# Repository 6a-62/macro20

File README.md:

# macro20

- 20 keys, intended for numpad/macropad layouts
- Designed for Pro Micro controller boards
- I2C header intended for 0.91 128\*32 OLED display
- PWM header for RGB LED lighting strip

Compatible with [QMK](https://qmk.fm)

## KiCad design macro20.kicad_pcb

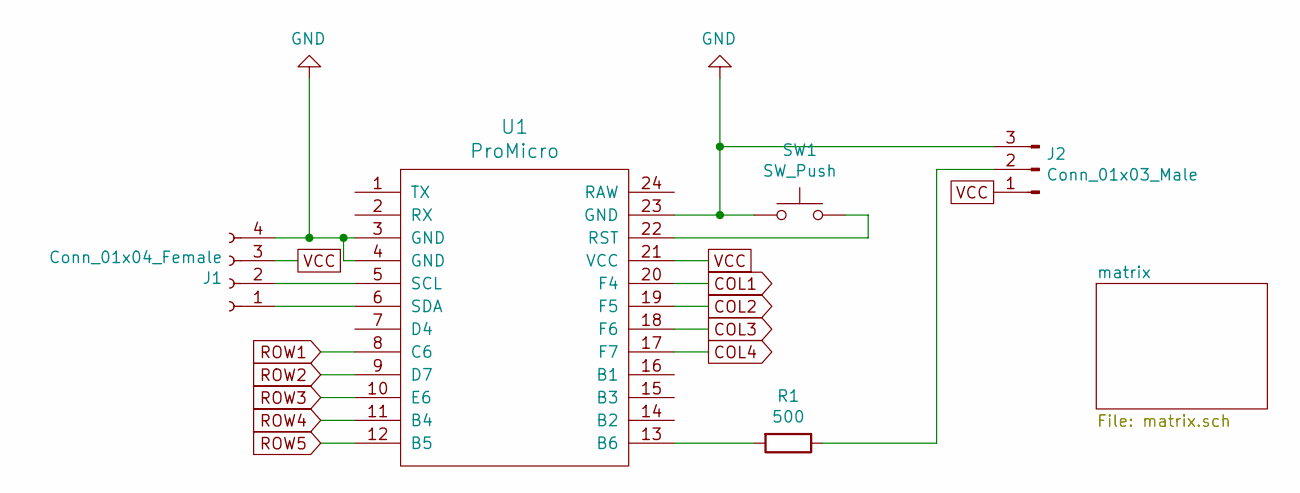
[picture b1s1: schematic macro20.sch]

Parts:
J1: Conn_01x04_Female; PinSocket_1x04_P2.54mm_Vertical
J2: Conn_01x03_Male; PinHeader_1x03_P2.54mm_Vertical
R1: 500; R_Axial_DIN0204_L3.6mm_D1.6mm_P5.08mm_Horizontal
SW1: SW_Push; SW_PUSH_6mm
U1: ProMicro

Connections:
COL1: U1.20 (F4); also elsewhere on the board
COL2: U1.19 (F5); also elsewhere on the board
COL3: U1.18 (F6); also elsewhere on the board
COL4: U1.17 (F7); also elsewhere on the board
GND: J1.4, J2.3, SW1.1, U1.3 (GND), U1.4 (GND), U1.23 (GND)
unnamed: J1.1, U1.6 (SDA)
unnamed: J1.2, U1.5 (SCL)
unnamed: J2.2, R1.1
unnamed: R1.2, U1.13 (B6)
unnamed: SW1.2, U1.22 (RST)
ROW1: U1.8 (C6); also elsewhere on the board
ROW2: U1.9 (D7); also elsewhere on the board
ROW3: U1.10 (E6); also elsewhere on the board
ROW4: U1.11 (B4); also elsewhere on the board
ROW5: U1.12 (B5); also elsewhere on the board
VCC: J1.3, J2.1, U1.21 (VCC)

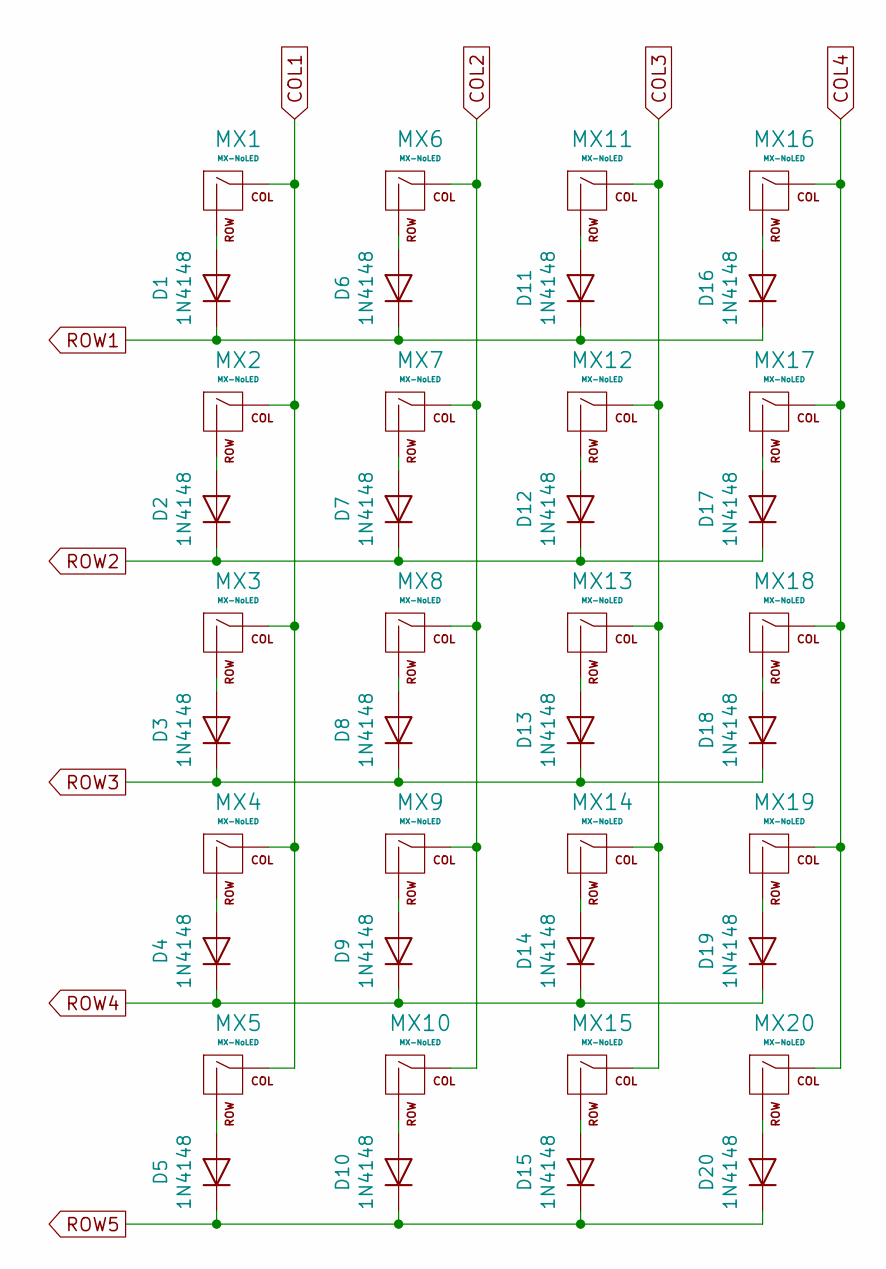
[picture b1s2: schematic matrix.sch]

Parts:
D1, D2, D3, D4, D5, D6, D7, D8, D9, D10, D11, D12, D13, D14, D15, D16, D17, D18, D19, D20: 1N4148; D_DO-35_SOD27_P7.62mm_Horizontal
MX1, MX2, MX3, MX4, MX5, MX6, MX7, MX8, MX9, MX10, MX11, MX12, MX13, MX14, MX15, MX16, MX17, MX18, MX19, MX20: MX-NoLED; MXOnly-1U-NoLED

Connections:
COL1: MX1.1 (COL), MX2.1 (COL), MX3.1 (COL), MX4.1 (COL), MX5.1 (COL); also elsewhere on the board
COL2: MX6.1 (COL), MX7.1 (COL), MX8.1 (COL), MX9.1 (COL), MX10.1 (COL); also elsewhere on the board
COL3: MX11.1 (COL), MX12.1 (COL), MX13.1 (COL), MX14.1 (COL), MX15.1 (COL); also elsewhere on the board
COL4: MX16.1 (COL), MX17.1 (COL), MX18.1 (COL), MX19.1 (COL), MX20.1 (COL); also elsewhere on the board
unnamed: D1.2 (A), MX1.2 (ROW)
unnamed: D2.2 (A), MX2.2 (ROW)
unnamed: D3.2 (A), MX3.2 (ROW)
unnamed: D4.2 (A), MX4.2 (ROW)
unnamed: D5.2 (A), MX5.2 (ROW)
unnamed: D6.2 (A), MX6.2 (ROW)
unnamed: D7.2 (A), MX7.2 (ROW)
unnamed: D8.2 (A), MX8.2 (ROW)
unnamed: D9.2 (A), MX9.2 (ROW)
unnamed: D10.2 (A), MX10.2 (ROW)
unnamed: D11.2 (A), MX11.2 (ROW)
unnamed: D12.2 (A), MX12.2 (ROW)
unnamed: D13.2 (A), MX13.2 (ROW)
unnamed: D14.2 (A), MX14.2 (ROW)
unnamed: D15.2 (A), MX15.2 (ROW)
unnamed: D16.2 (A), MX16.2 (ROW)
unnamed: D17.2 (A), MX17.2 (ROW)
unnamed: D18.2 (A), MX18.2 (ROW)
unnamed: D19.2 (A), MX19.2 (ROW)
unnamed: D20.2 (A), MX20.2 (ROW)
ROW1: D1.1 (K), D6.1 (K), D11.1 (K), D16.1 (K); also elsewhere on the board
ROW2: D2.1 (K), D7.1 (K), D12.1 (K), D17.1 (K); also elsewhere on the board
ROW3: D3.1 (K), D8.1 (K), D13.1 (K), D18.1 (K); also elsewhere on the board
ROW4: D4.1 (K), D9.1 (K), D14.1 (K), D19.1 (K); also elsewhere on the board
ROW5: D5.1 (K), D10.1 (K), D15.1 (K), D20.1 (K); also elsewhere on the board

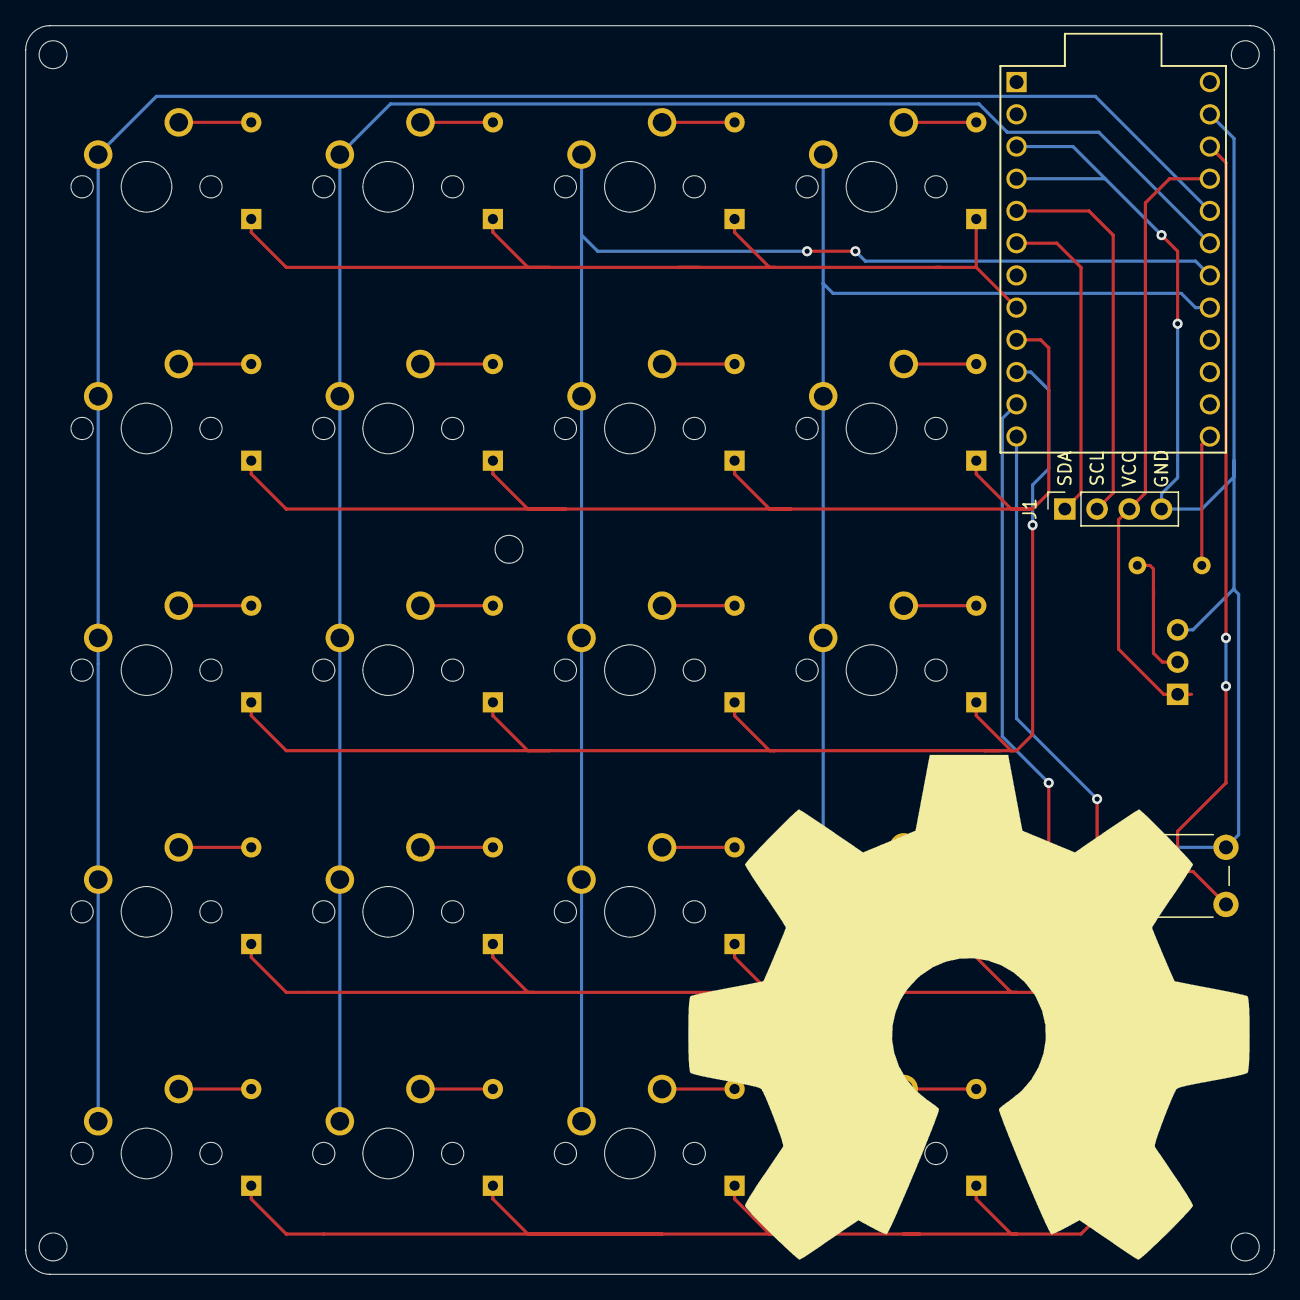
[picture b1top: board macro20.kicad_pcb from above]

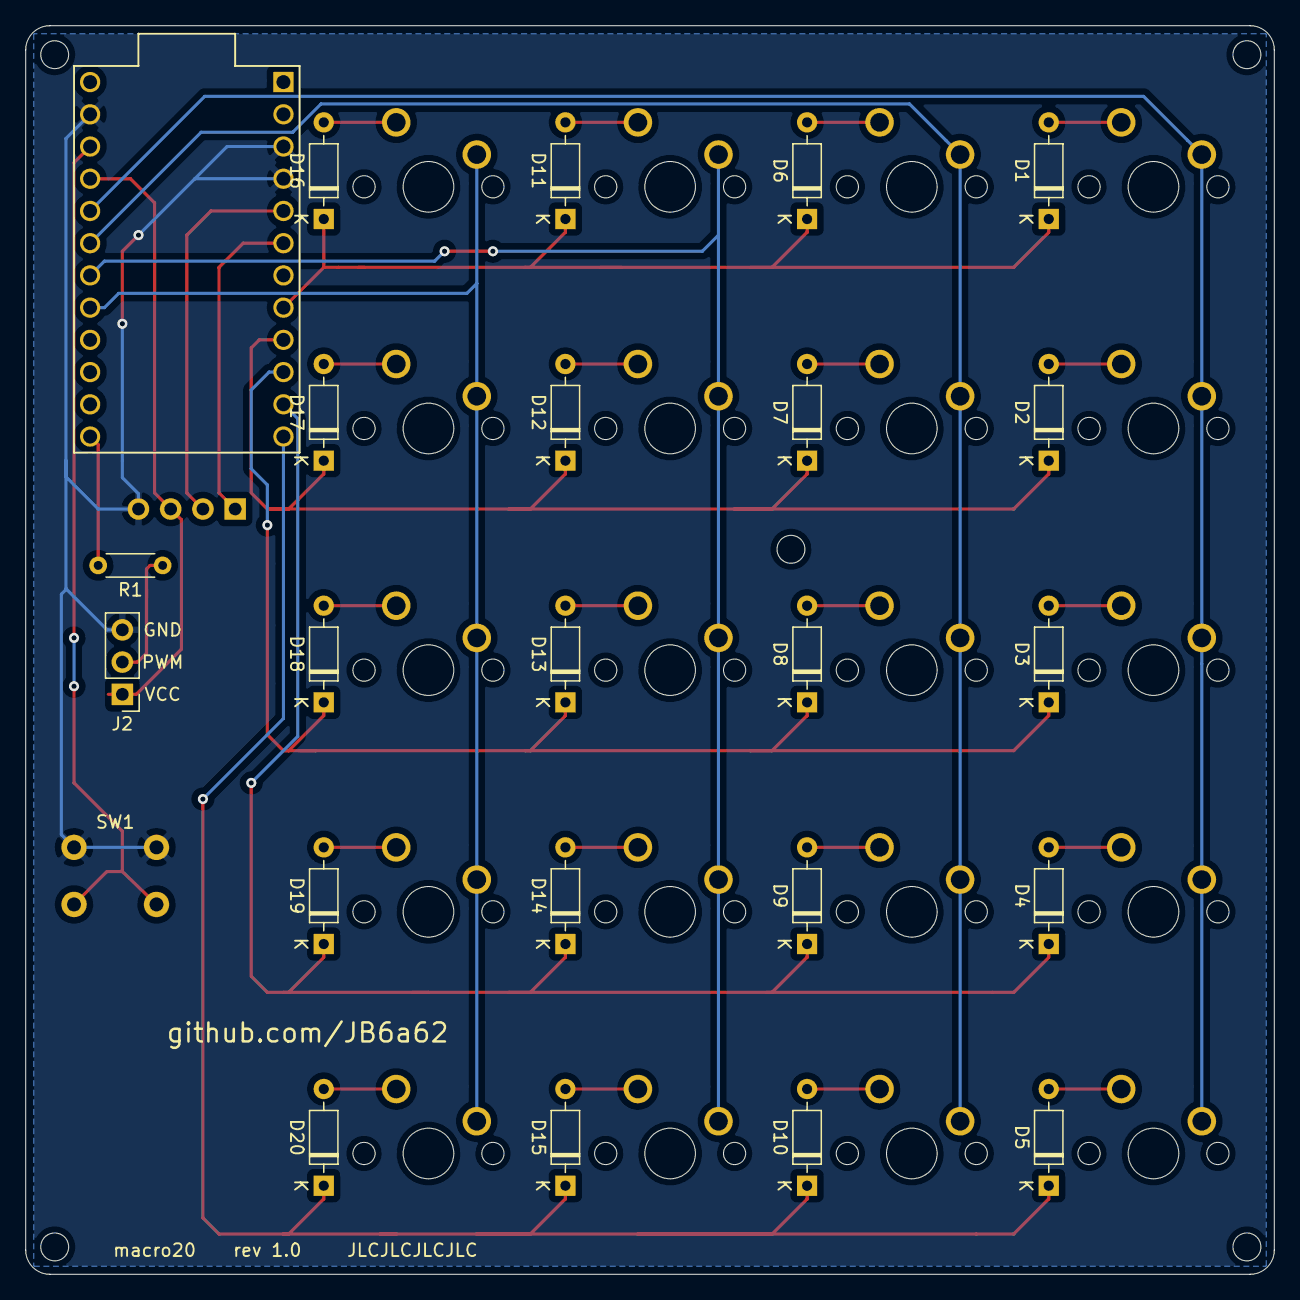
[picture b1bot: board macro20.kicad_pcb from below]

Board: 2 copper layers, 98.4 x 98.4 mm, 45 parts (22 on the bottom side), 36 nets.

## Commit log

2020-01-22 Add submodules
2020-01-22 Add board files
2020-01-22 Add gerber files
2020-01-22 Add render image
2020-01-22 Update board
2020-01-22 Silkscreen/mask graphics
2020-01-22 Silkscreen/mask changes
